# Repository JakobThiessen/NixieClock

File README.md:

# NixieClock

# Hardware

Wichtig: Ohne Änderung tut die SD karte nicht. (Betrifft nur V2.0 in der V2.1 sind die Änderung im Layout schon umgesetzt)

## Display 1.14"

| Top side                |Bottom side               |
|-----------------------:|:-------------------------:|
|  |  |

## Display 1.8"

| Top side                |Bottom side               |
|-----------------------:|:-------------------------:|
|  |  |

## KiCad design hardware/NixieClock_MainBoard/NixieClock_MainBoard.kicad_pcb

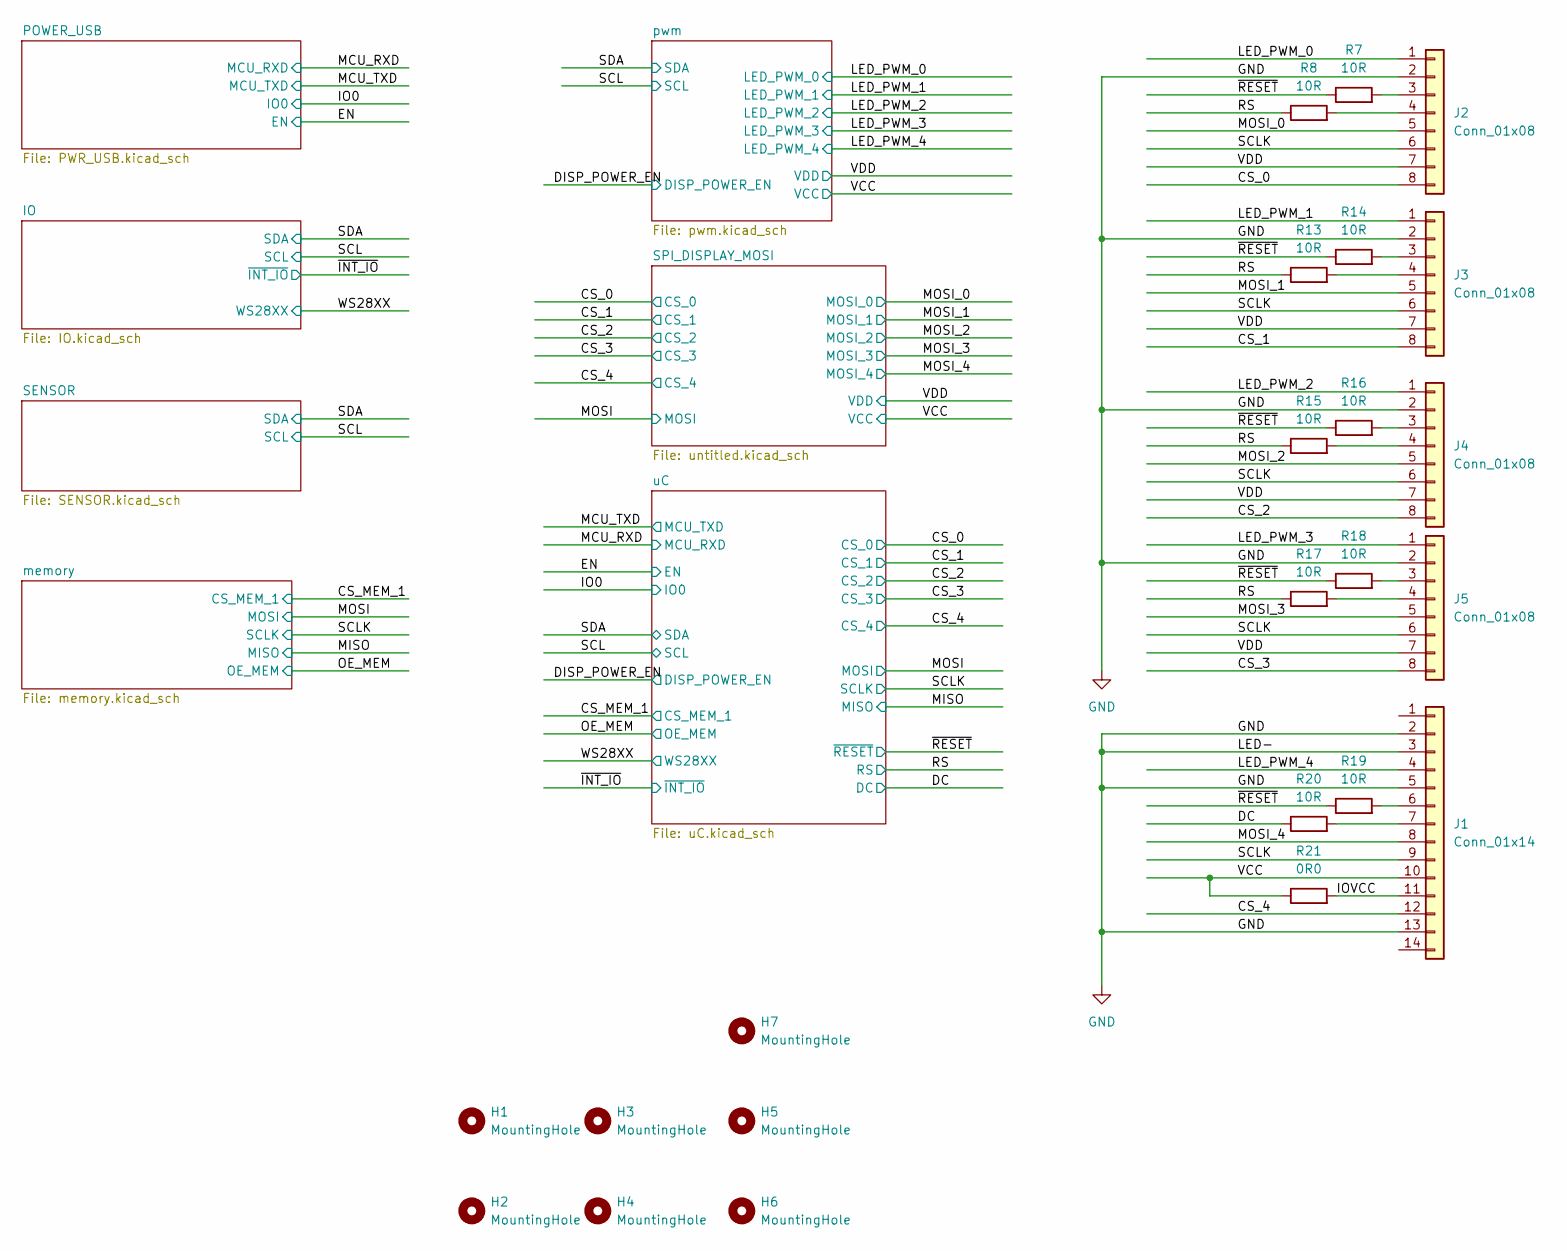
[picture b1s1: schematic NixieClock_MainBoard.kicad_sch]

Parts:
H1, H2, H3, H4, H5, H6, H7: MountingHole; MountingHole_3.2mm_M3
J1: Conn_01x14; PinSocket_1x14_P1.27mm_Vertical
J2, J3, J4, J5: Conn_01x08; PinSocket_1x08_P1.27mm_Vertical
R7, R8, R13, R14, R15, R16, R17, R18, R19, R20: 10R; R_0603_1608Metric
R21: 0R0; R_0603_1608Metric

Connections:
/CS_0: J2.8; also elsewhere on the board
/CS_1: J3.8; also elsewhere on the board
/CS_2: J4.8; also elsewhere on the board
/CS_3: J5.8; also elsewhere on the board
/CS_4: J1.12; also elsewhere on the board
/DC: R20.1; also elsewhere on the board
/IOVCC: J1.11, R21.2
/LED_PWM_0: J2.1; also elsewhere on the board
/LED_PWM_1: J3.1; also elsewhere on the board
/LED_PWM_2: J4.1; also elsewhere on the board
/LED_PWM_3: J5.1; also elsewhere on the board
/LED_PWM_4: J1.4; also elsewhere on the board
/MOSI_0: J2.5; also elsewhere on the board
/MOSI_1: J3.5; also elsewhere on the board
/MOSI_2: J4.5; also elsewhere on the board
/MOSI_3: J5.5; also elsewhere on the board
/MOSI_4: J1.8; also elsewhere on the board
/RS: R8.1, R13.1, R15.1, R17.1; also elsewhere on the board
/SCLK: J1.9, J2.6, J3.6, J4.6, J5.6; also elsewhere on the board
/VCC: J1.10, R21.1; also elsewhere on the board
/VDD: J2.7, J3.7, J4.7, J5.7; also elsewhere on the board
/~RESET: R7.1, R14.1, R16.1, R18.1, R19.1; also elsewhere on the board
GND: J1.2, J1.3, J1.5, J1.13, J2.2, J3.2, J4.2, J5.2; also elsewhere on the board
unnamed: J1.6, R19.2
unnamed: J1.7, R20.2
unnamed: J2.3, R7.2
unnamed: J2.4, R8.2
unnamed: J3.3, R14.2
unnamed: J3.4, R13.2
unnamed: J4.3, R16.2
unnamed: J4.4, R15.2
unnamed: J5.3, R18.2
unnamed: J5.4, R17.2

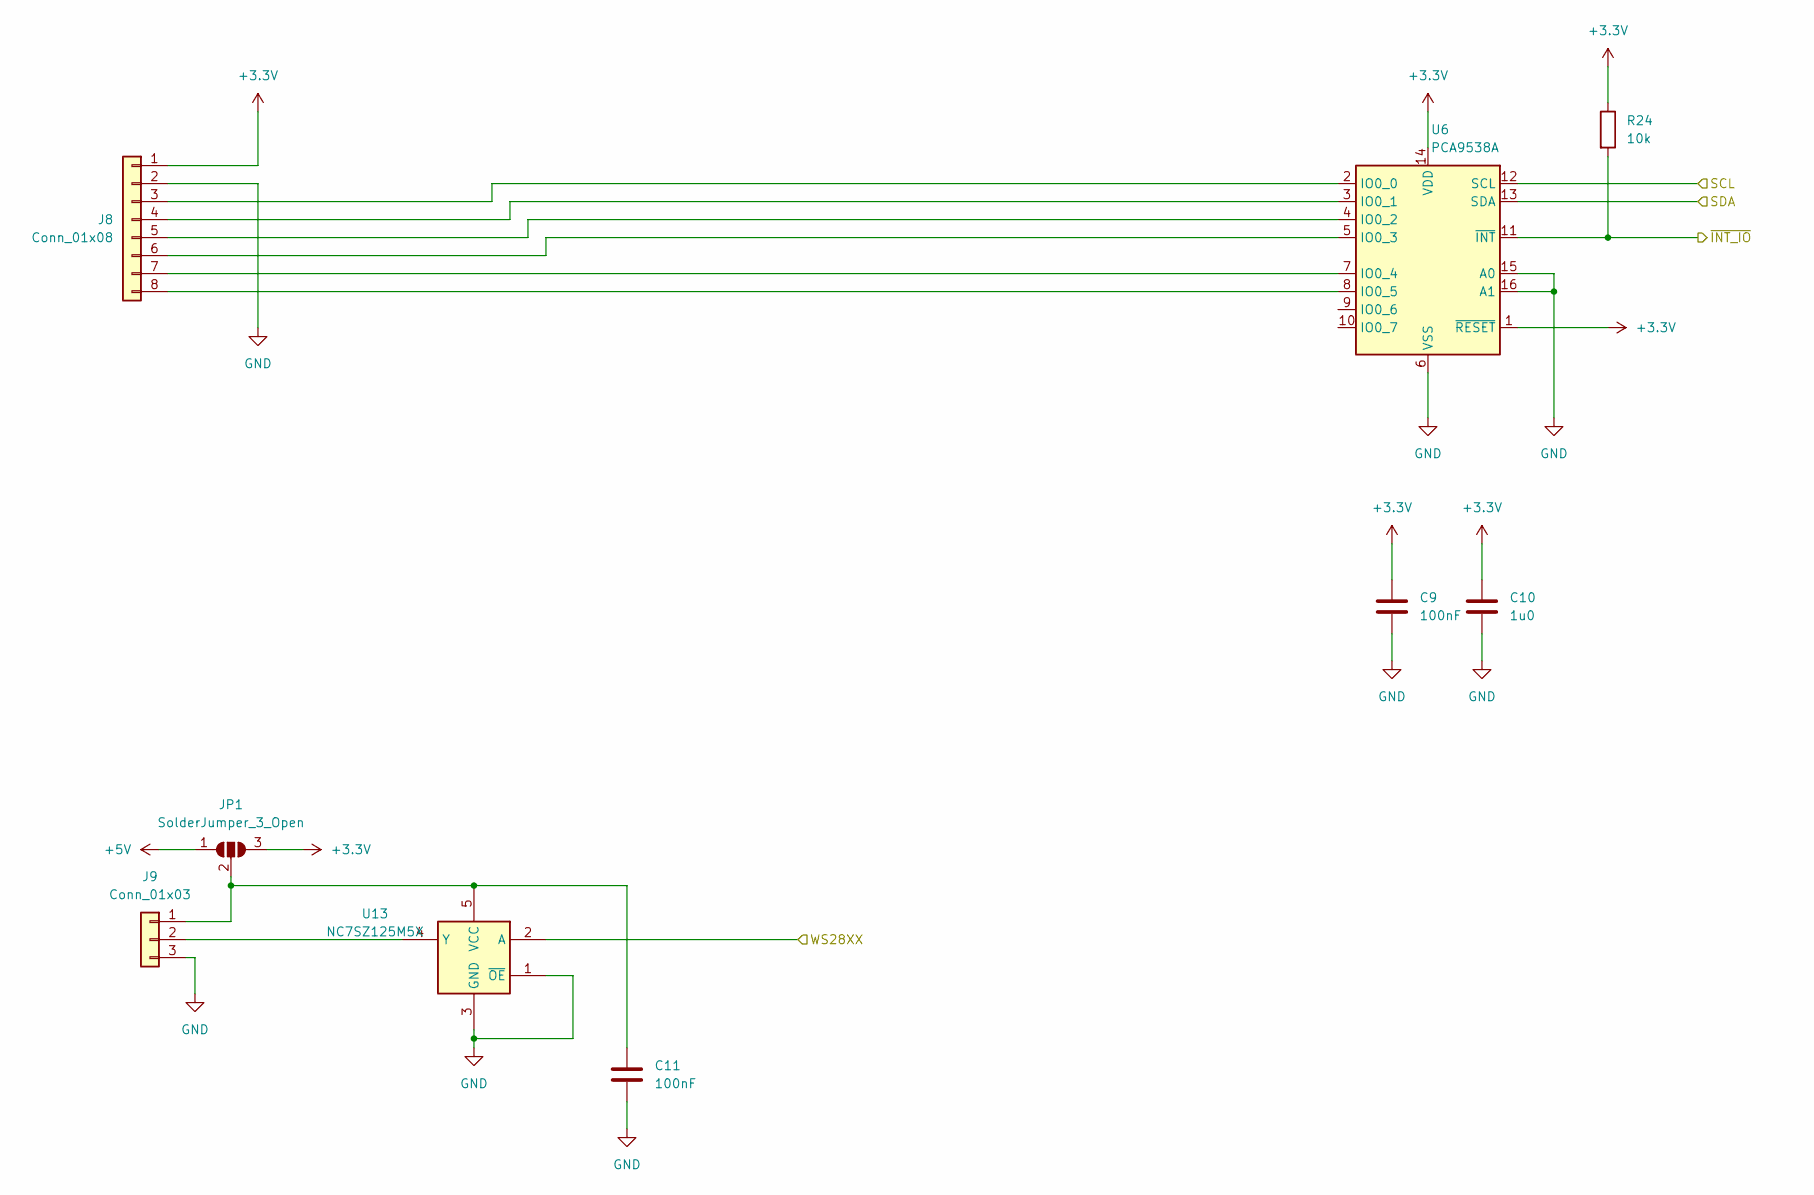
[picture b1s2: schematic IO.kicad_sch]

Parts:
C9, C11: 100nF; C_0603_1608Metric
C10: 1u0; C_0603_1608Metric
J8: Conn_01x08; PinHeader_1x08_P2.54mm_Vertical
J9: Conn_01x03; PinHeader_1x03_P2.54mm_Vertical
JP1: SolderJumper_3_Open; SolderJumper-3_P1.3mm_Open_Pad1.0x1.5mm
R24: 10k; R_0603_1608Metric
U6: PCA9538A; HVQFN-16-1EP_3x3mm_P0.5mm_EP1.5x1.5mm
U13: NC7SZ125M5X; SOT-23-5

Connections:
+3.3V: C9.1, C10.1, J8.1, JP1.3 (B), R24.1, U6.1 (~RESET), U6.14 (VDD); also elsewhere on the board
+5V: JP1.1 (A); also elsewhere on the board
/SCL: U6.12 (SCL); also elsewhere on the board
/SDA: U6.13 (SDA); also elsewhere on the board
/WS28XX: U13.2 (A); also elsewhere on the board
/~INT_IO: R24.2, U6.11 (~INT); also elsewhere on the board
GND: C9.2, C10.2, C11.2, J8.2, J9.3, U6.6 (VSS), U6.15 (A0), U6.16 (A1), U13.1 (~OE), U13.3 (GND); also elsewhere on the board
unnamed: J8.3, U6.2 (IO0_0)
unnamed: J8.4, U6.3 (IO0_1)
unnamed: J8.5, U6.4 (IO0_2)
unnamed: J8.6, U6.5 (IO0_3)
unnamed: J8.7, U6.7 (IO0_4)
unnamed: J8.8, U6.8 (IO0_5)
unnamed: C11.1, J9.1, JP1.2 (C), U13.5 (VCC)
unnamed: J9.2, U13.4 (Y)

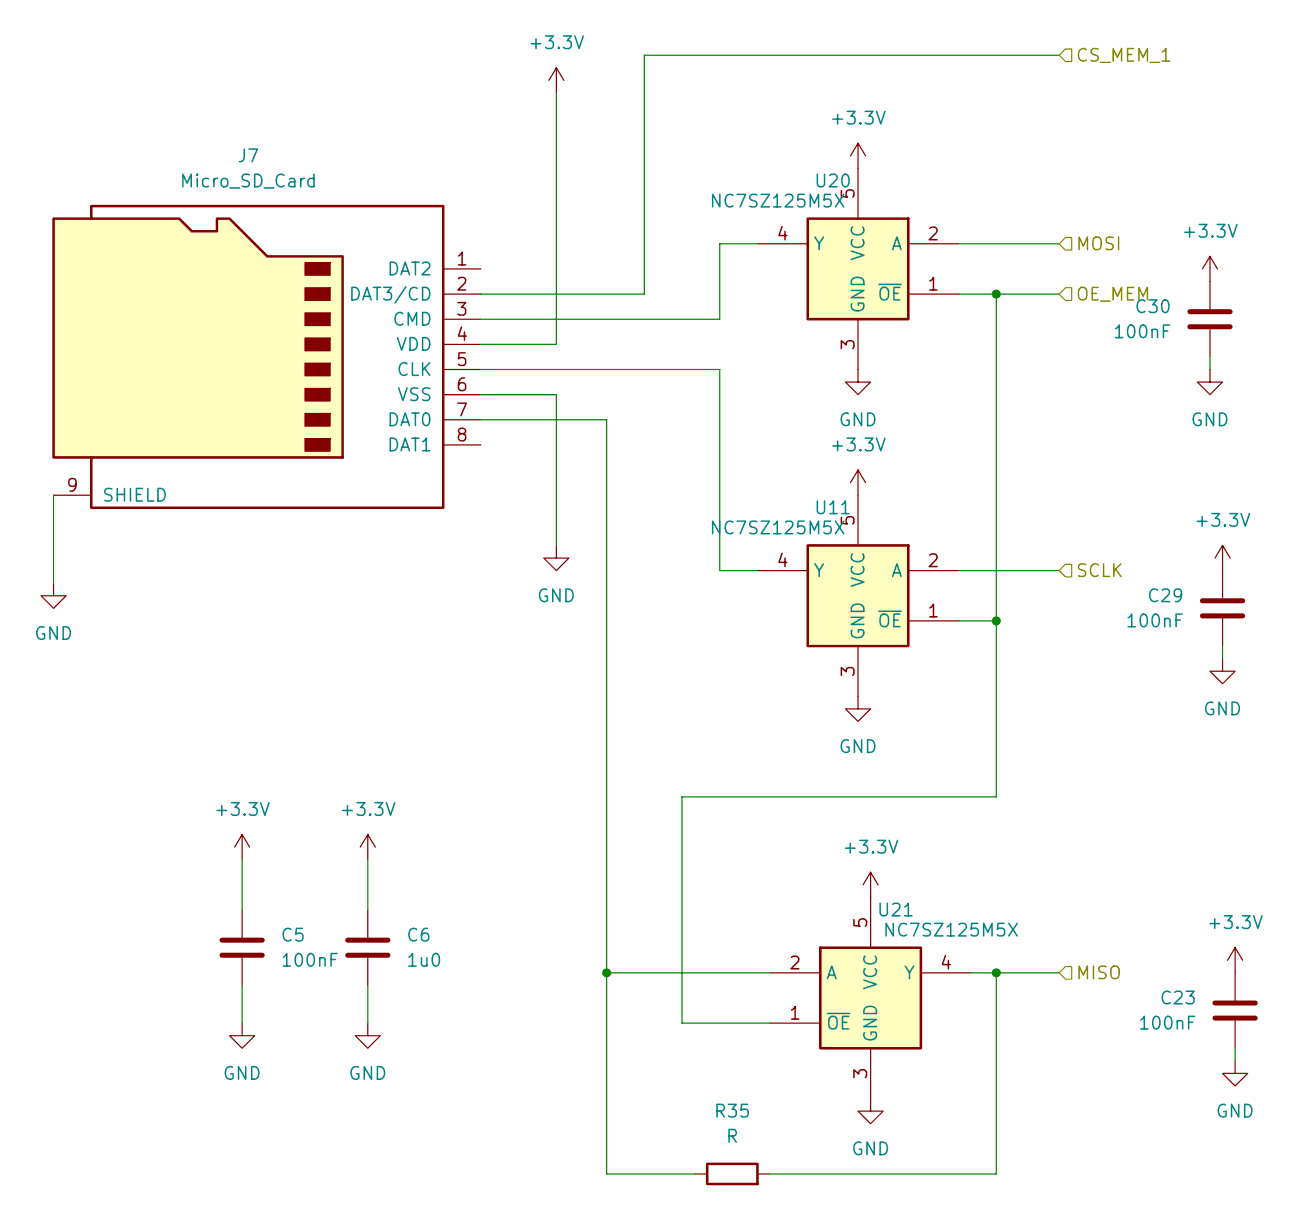
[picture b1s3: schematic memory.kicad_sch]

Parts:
C5, C23, C29, C30: 100nF; C_0603_1608Metric
C6: 1u0; C_0603_1608Metric
J7: Micro_SD_Card; microSD_HC_Hirose_DM3D-SF
R35: R; R_0603_1608Metric
U11, U20, U21: NC7SZ125M5X; SOT-23-5

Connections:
+3.3V: C5.1, C6.1, C23.1, C29.1, C30.1, J7.4 (VDD), U11.5 (VCC), U20.5 (VCC), U21.5 (VCC); also elsewhere on the board
/CS_MEM_1: J7.2 (DAT3/CD); also elsewhere on the board
/MISO: R35.2, U21.4 (Y); also elsewhere on the board
/MOSI: U20.2 (A); also elsewhere on the board
/OE_MEM: U11.1 (~OE), U20.1 (~OE), U21.1 (~OE); also elsewhere on the board
/SCLK: U11.2 (A); also elsewhere on the board
GND: C5.2, C6.2, C23.2, C29.2, C30.2, J7.6 (VSS), J7.9 (SHIELD), U11.3 (GND), U20.3 (GND), U21.3 (GND); also elsewhere on the board
unnamed: J7.5 (CLK), U11.4 (Y)
unnamed: J7.3 (CMD), U20.4 (Y)
unnamed: J7.7 (DAT0), R35.1, U21.2 (A)

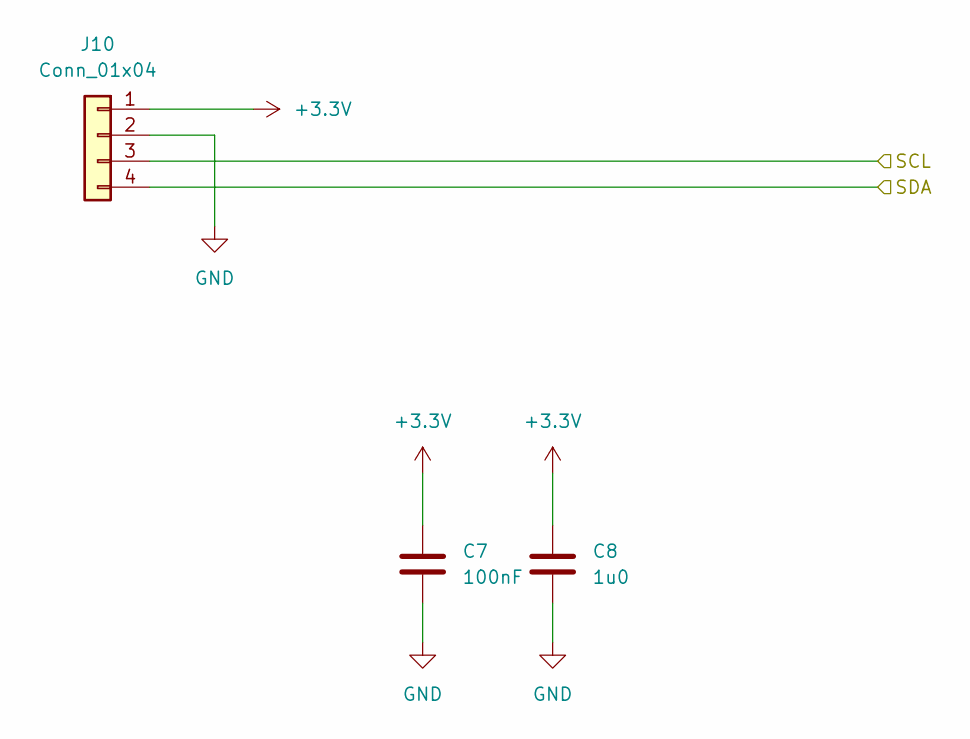
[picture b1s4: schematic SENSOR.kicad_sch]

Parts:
C7: 100nF; C_0603_1608Metric
C8: 1u0; C_0603_1608Metric
J10: Conn_01x04; PinHeader_1x04_P2.54mm_Vertical

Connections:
+3.3V: C7.1, C8.1, J10.1; also elsewhere on the board
/SCL: J10.3; also elsewhere on the board
/SDA: J10.4; also elsewhere on the board
GND: C7.2, C8.2, J10.2; also elsewhere on the board

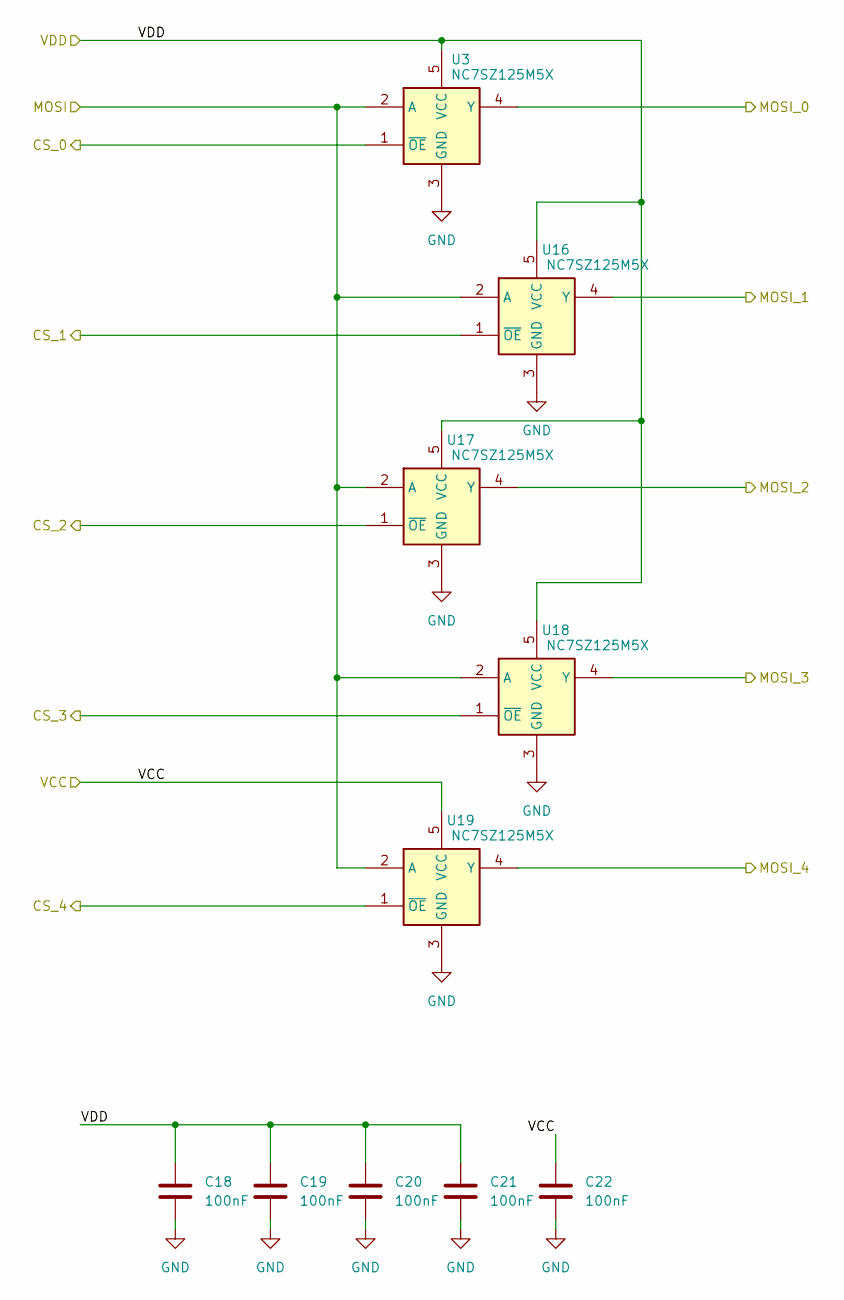
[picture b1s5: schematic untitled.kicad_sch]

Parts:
C18, C19, C20, C21, C22: 100nF; C_0603_1608Metric
U3, U16, U17, U18, U19: NC7SZ125M5X; SOT-23-5

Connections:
/CS_0: U3.1 (~OE); also elsewhere on the board
/CS_1: U16.1 (~OE); also elsewhere on the board
/CS_2: U17.1 (~OE); also elsewhere on the board
/CS_3: U18.1 (~OE); also elsewhere on the board
/CS_4: U19.1 (~OE); also elsewhere on the board
/MOSI: U3.2 (A), U16.2 (A), U17.2 (A), U18.2 (A), U19.2 (A); also elsewhere on the board
/MOSI_0: U3.4 (Y); also elsewhere on the board
/MOSI_1: U16.4 (Y); also elsewhere on the board
/MOSI_2: U17.4 (Y); also elsewhere on the board
/MOSI_3: U18.4 (Y); also elsewhere on the board
/MOSI_4: U19.4 (Y); also elsewhere on the board
/VCC: C22.1, U19.5 (VCC); also elsewhere on the board
/VDD: C18.1, C19.1, C20.1, C21.1, U3.5 (VCC), U16.5 (VCC), U17.5 (VCC), U18.5 (VCC); also elsewhere on the board
GND: C18.2, C19.2, C20.2, C21.2, C22.2, U3.3 (GND), U16.3 (GND), U17.3 (GND), U18.3 (GND), U19.3 (GND); also elsewhere on the board

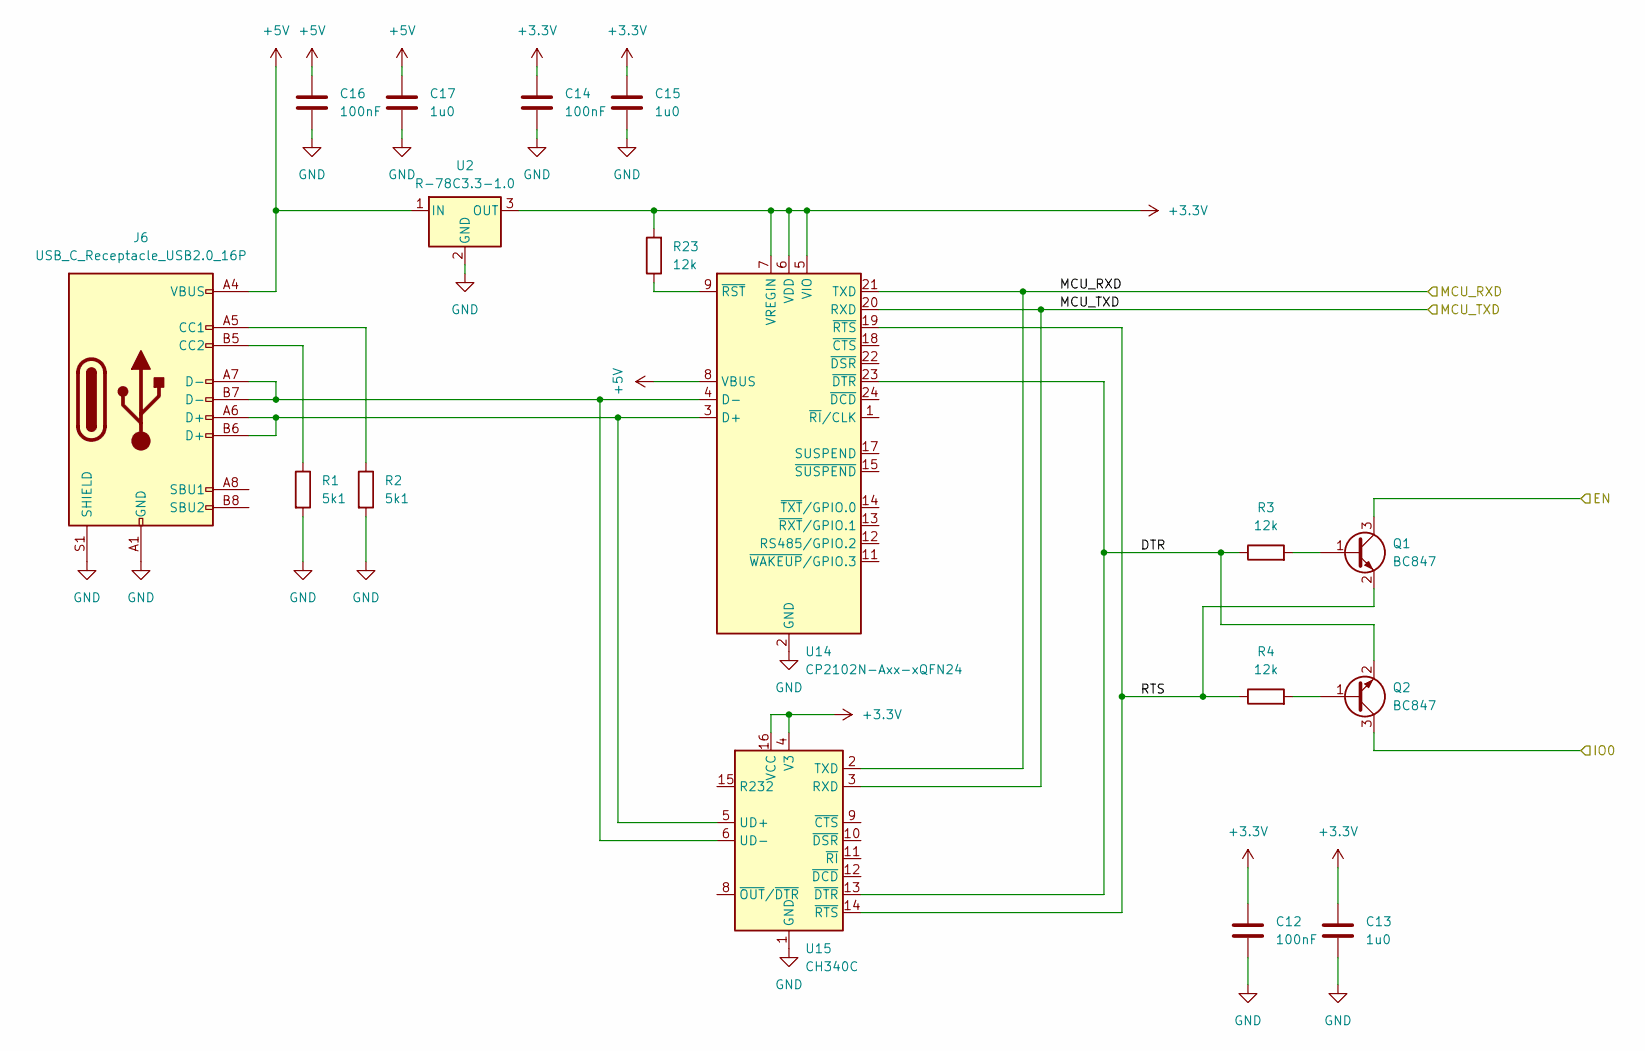
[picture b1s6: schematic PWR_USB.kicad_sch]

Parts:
C12, C14, C16: 100nF; C_0603_1608Metric
C13, C15, C17: 1u0; C_0603_1608Metric
J6: USB_C_Receptacle_USB2.0_16P; USB_C_Receptacle_GCT_USB4110
Q1, Q2: BC847; SOT-23
R1, R2: 5k1; R_0603_1608Metric
R3, R4, R23: 12k; R_0603_1608Metric
U2: R-78C3.3-1.0; Converter_DCDC_RECOM_R-78E-0.5_THT
U14: CP2102N-Axx-xQFN24; QFN-24-1EP_4x4mm_P0.5mm_EP2.6x2.6mm
U15: CH340C; SOIC-16_3.9x9.9mm_P1.27mm

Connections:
+3.3V: C12.1, C13.1, C14.1, C15.1, R23.2, U2.3 (OUT), U14.5 (VIO), U14.6 (VDD), U14.7 (VREGIN), U15.4 (V3), U15.16 (VCC); also elsewhere on the board
+5V: C16.1, C17.1, J6.A4 (VBUS), J6.A9 (VBUS), J6.B4 (VBUS), J6.B9 (VBUS), U2.1 (IN), U14.8 (VBUS); also elsewhere on the board
/EN: Q1.3 (C); also elsewhere on the board
/IO0: Q2.3 (C); also elsewhere on the board
/MCU_RXD: U14.21 (TXD), U15.2 (TXD); also elsewhere on the board
/MCU_TXD: U14.20 (RXD), U15.3 (RXD); also elsewhere on the board
/POWER_USB/DTR: Q2.2 (E), R3.1, U14.23 (~DTR), U15.13 (~DTR)
/POWER_USB/RTS: Q1.2 (E), R4.1, U14.19 (~RTS), U15.14 (~RTS)
GND: C12.2, C13.2, C14.2, C15.2, C16.2, C17.2, J6.A1 (GND), J6.A12 (GND), J6.B1 (GND), J6.B12 (GND), J6.S1 (SHIELD), R1.2, R2.2, U2.2 (GND), U14.2 (GND), U14.25 (GND), U15.1 (GND); also elsewhere on the board
unnamed: J6.A5 (CC1), R2.1
unnamed: J6.B5 (CC2), R1.1
unnamed: Q1.1 (B), R3.2
unnamed: Q2.1 (B), R4.2
unnamed: J6.A6 (D+), J6.B6 (D+), U14.3 (D+), U15.5 (UD+)
unnamed: J6.A7 (D-), J6.B7 (D-), U14.4 (D-), U15.6 (UD-)
unnamed: R23.1, U14.9 (~RST)

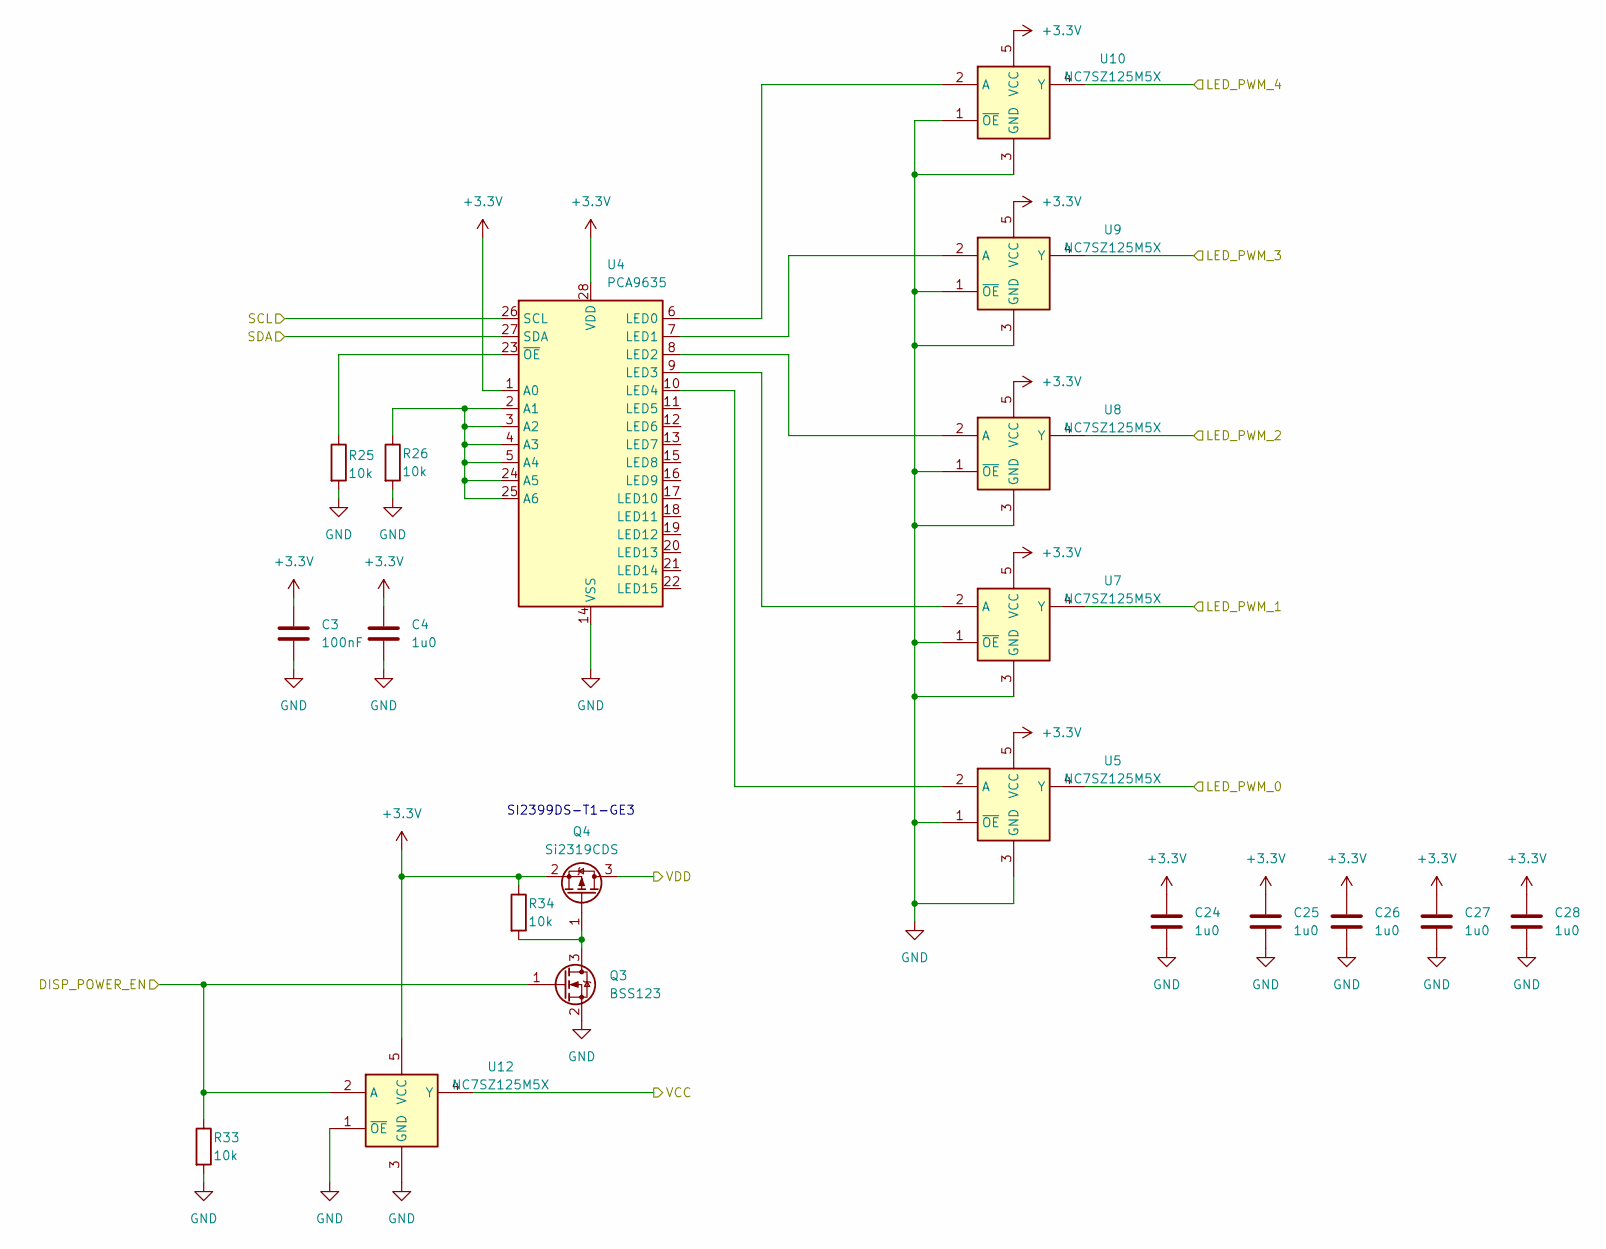
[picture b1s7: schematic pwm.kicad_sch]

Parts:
C3: 100nF; C_0603_1608Metric
C4, C24, C25, C26, C27, C28: 1u0; C_0603_1608Metric
Q3: BSS123; SOT-23
Q4: Si2319CDS; SOT-23
R25, R26, R33, R34: 10k; R_0603_1608Metric
U4: PCA9635; TSSOP-28_4.4x9.7mm_P0.65mm
U5, U7, U8, U9, U10, U12: NC7SZ125M5X; SOT-23-5

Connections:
+3.3V: C3.1, C4.1, C24.1, C25.1, C26.1, C27.1, C28.1, Q4.2 (S), R34.1, U4.1 (A0), U4.28 (VDD), U5.5 (VCC), U7.5 (VCC), U8.5 (VCC), U9.5 (VCC), U10.5 (VCC), U12.5 (VCC); also elsewhere on the board
/DISP_POWER_EN: Q3.1 (G), R33.1, U12.2 (A); also elsewhere on the board
/LED_PWM_0: U5.4 (Y); also elsewhere on the board
/LED_PWM_1: U7.4 (Y); also elsewhere on the board
/LED_PWM_2: U8.4 (Y); also elsewhere on the board
/LED_PWM_3: U9.4 (Y); also elsewhere on the board
/LED_PWM_4: U10.4 (Y); also elsewhere on the board
/SCL: U4.26 (SCL); also elsewhere on the board
/SDA: U4.27 (SDA); also elsewhere on the board
/VCC: U12.4 (Y); also elsewhere on the board
/VDD: Q4.3 (D); also elsewhere on the board
GND: C3.2, C4.2, C24.2, C25.2, C26.2, C27.2, C28.2, Q3.2 (S), R25.2, R26.2, R33.2, U4.14 (VSS), U5.1 (~OE), U5.3 (GND), U7.1 (~OE), U7.3 (GND), U8.1 (~OE), U8.3 (GND), U9.1 (~OE), U9.3 (GND), U10.1 (~OE), U10.3 (GND), U12.1 (~OE), U12.3 (GND); also elsewhere on the board
unnamed: Q3.3 (D), Q4.1 (G), R34.2
unnamed: R26.1, U4.2 (A1), U4.3 (A2), U4.4 (A3), U4.5 (A4), U4.24 (A5), U4.25 (A6)
unnamed: U4.7 (LED1), U9.2 (A)
unnamed: U4.8 (LED2), U8.2 (A)
unnamed: U4.9 (LED3), U7.2 (A)
unnamed: U4.10 (LED4), U5.2 (A)
unnamed: R25.1, U4.23 (~OE)
unnamed: U4.6 (LED0), U10.2 (A)

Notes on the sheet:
SI2399DS-T1-GE3

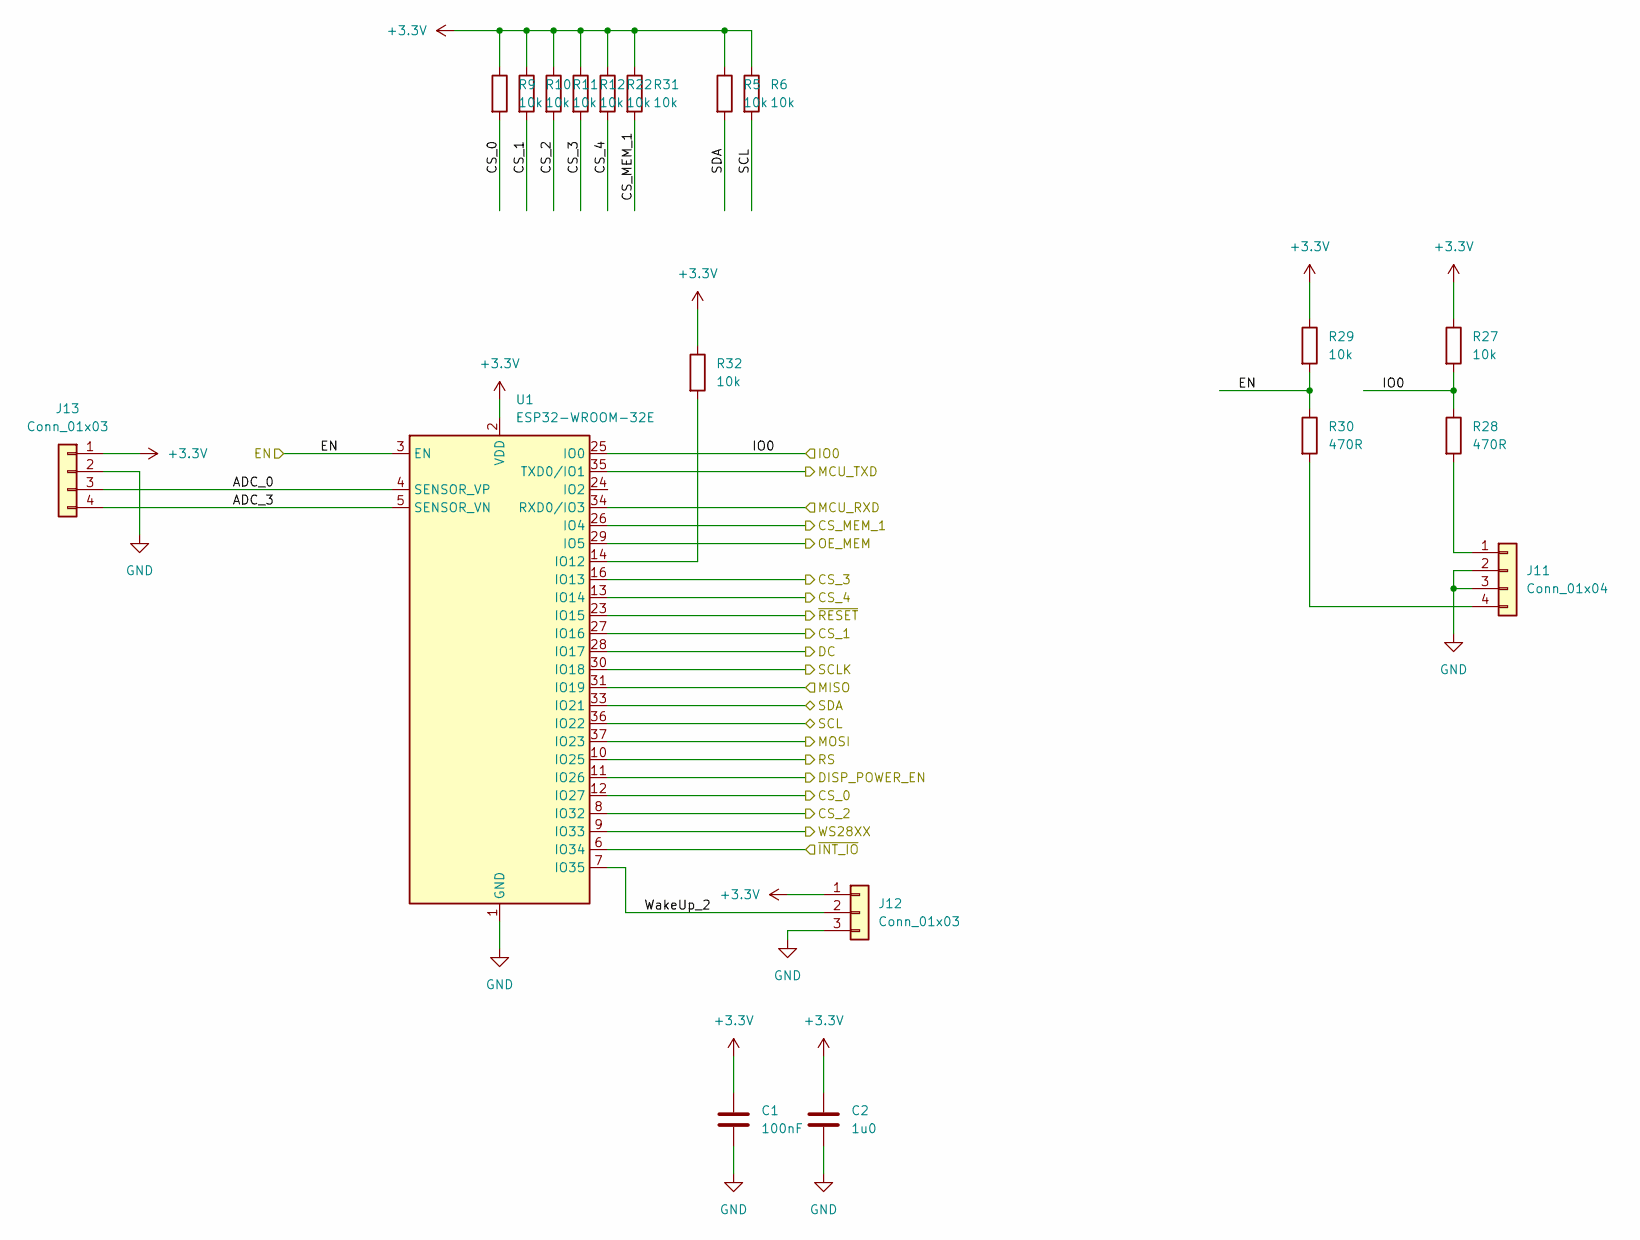
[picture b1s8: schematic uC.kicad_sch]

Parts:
C1: 100nF; C_0603_1608Metric
C2: 1u0; C_0603_1608Metric
J11: Conn_01x04; PinHeader_1x04_P2.54mm_Vertical_SMD_Pin1Left
J12: Conn_01x03; PinHeader_1x03_P2.54mm_Vertical
J13: Conn_01x03; PinHeader_1x04_P2.54mm_Vertical
R5, R6, R9, R10, R11, R12, R22, R27, R29, R31, R32: 10k; R_0603_1608Metric
R28, R30: 470R; R_0603_1608Metric
U1: ESP32-WROOM-32E; ESP32-WROOM-32D

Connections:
+3.3V: C1.1, C2.1, J12.1, J13.1, R5.1, R6.1, R9.1, R10.1, R11.1, R12.1, R22.1, R27.1, R29.1, R31.1, R32.1, U1.2 (VDD); also elsewhere on the board
/CS_0: R9.2, U1.12 (IO27); also elsewhere on the board
/CS_1: R10.2, U1.27 (IO16); also elsewhere on the board
/CS_2: R11.2, U1.8 (IO32); also elsewhere on the board
/CS_3: R12.2, U1.16 (IO13); also elsewhere on the board
/CS_4: R22.2, U1.13 (IO14); also elsewhere on the board
/CS_MEM_1: R31.2, U1.26 (IO4); also elsewhere on the board
/DC: U1.28 (IO17); also elsewhere on the board
/DISP_POWER_EN: U1.11 (IO26); also elsewhere on the board
/EN: R29.2, R30.1, U1.3 (EN); also elsewhere on the board
/IO0: R27.2, R28.1, U1.25 (IO0); also elsewhere on the board
/MCU_RXD: U1.34 (RXD0/IO3); also elsewhere on the board
/MCU_TXD: U1.35 (TXD0/IO1); also elsewhere on the board
/MISO: U1.31 (IO19); also elsewhere on the board
/MOSI: U1.37 (IO23); also elsewhere on the board
/OE_MEM: U1.29 (IO5); also elsewhere on the board
/RS: U1.10 (IO25); also elsewhere on the board
/SCL: R6.2, U1.36 (IO22); also elsewhere on the board
/SCLK: U1.30 (IO18); also elsewhere on the board
/SDA: R5.2, U1.33 (IO21); also elsewhere on the board
/WS28XX: U1.9 (IO33); also elsewhere on the board
/uC/ADC_0: J13.3, U1.4 (SENSOR_VP)
/uC/ADC_3: J13.4, U1.5 (SENSOR_VN)
/uC/WakeUp_2: J12.2, U1.7 (IO35)
/~INT_IO: U1.6 (IO34); also elsewhere on the board
/~RESET: U1.23 (IO15); also elsewhere on the board
GND: C1.2, C2.2, J11.2, J11.3, J12.3, J13.2, U1.1 (GND), U1.15 (GND), U1.38 (GND), U1.39 (GND); also elsewhere on the board
unnamed: J11.1, R28.2
unnamed: J11.4, R30.2
unnamed: R32.2, U1.14 (IO12)

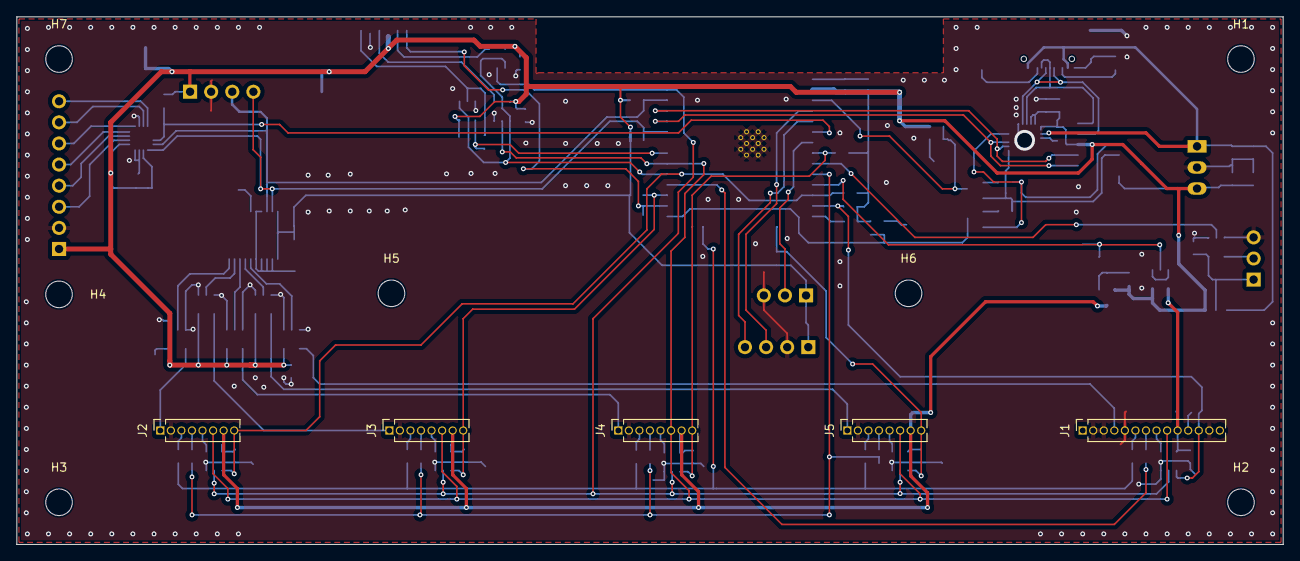
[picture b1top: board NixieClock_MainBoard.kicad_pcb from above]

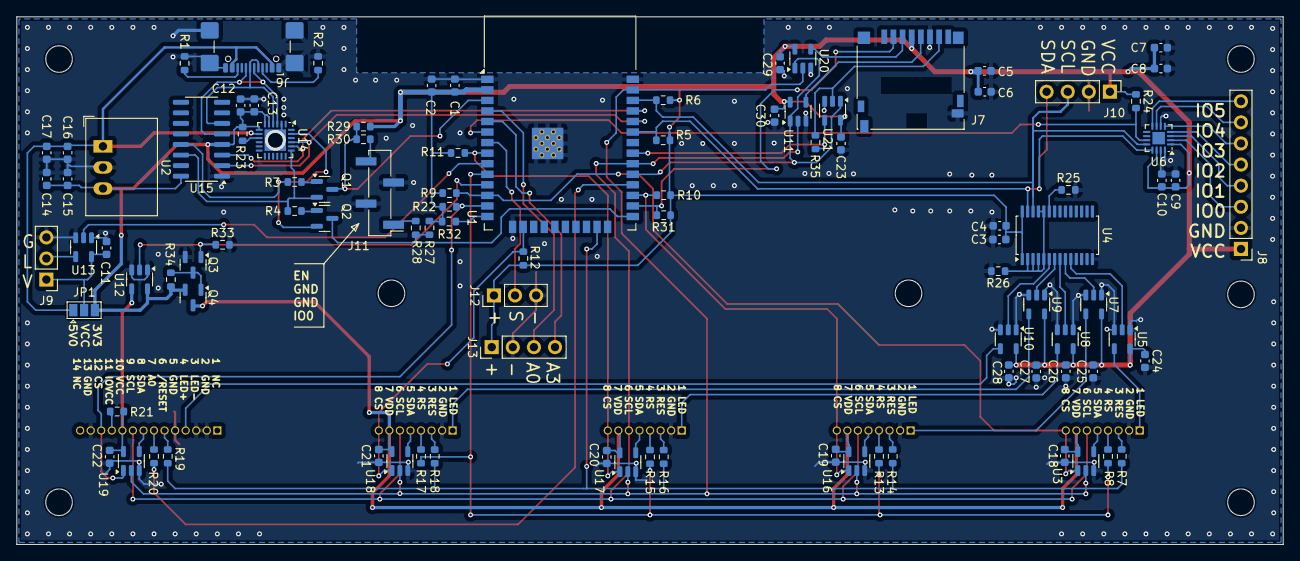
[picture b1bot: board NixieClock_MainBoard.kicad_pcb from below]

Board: 2 copper layers, 152.4 x 63.5 mm, 111 parts (99 on the bottom side), 82 nets.

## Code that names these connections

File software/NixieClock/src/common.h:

#ifndef COMMON_CONFIG_h
#define COMMON_CONFIG_h

#include <stdint.h>
#include "freertos/FreeRTOS.h"
#include "freertos/FreeRTOSConfig.h"
#include "freertos/task.h"
#include "freertos/queue.h"

#include <time.h>

#ifdef __cplusplus
extern "C" {
#endif

/**************************** */
/*** DEFINES              *** */
/**************************** */

#define CONFIG_FREERTOS_USE_STATS_FORMATTING_FUNCTIONS 1
#define CONFIG_FREERTOS_USE_TRACE_FACILITY 1

#define TFT_MOSI        23
#define TFT_MISO        19
#define TFT_CLK         18
#define TFT_RST         -1 // set to -1 and connect to Arduino RESET pin
#define TFT_DC          25
#define TFT_DC_2        17
#define TFT_RESET       15

#define TFT_CS_0        27
#define TFT_CS_1        16
#define TFT_CS_2        32
#define TFT_CS_3        13
#define TFT_CS_4        14

#define SD_CS           5
#define SD_BUF_OE       4   // /OE der 74LVC1G125 Tristate-Buffer (LOW=aktiv)
#define DISPLAY_POW_EN  26

#define LED_PIN         33

#define INT_IO_PIN      34
#define WAKE_UP_PIN     35

#define ADC_0_PIN       36  // ADC1
#define ADC_3_PIN       39  // ADC1

#define SPI_FREQUENCY 16000000U

// ─── I2C bus (PCA9538A button expander + PCA9685 backlight) ──────────────────
#define I2C_SDA_PIN     21
#define I2C_SCL_PIN     22

#define FW_VERSION "5.12.0"
#define FW_BUILD_DATE __DATE__
#define FW_BUILD_TIME __TIME__

#define SD_CACHE_MAX 128

// SD background image limits (24-bit BMP only)
#define BG_IMAGE_MAX_FILE_SIZE  (100UL * 1024UL)  // max file size on SD
#define BG_IMAGE_MAX_W          160               // max image width  (px)
#define BG_IMAGE_MAX_H          128               // max image height (px)



typedef struct {
    char path[128];
    char name[64];
    bool isDir;
    uint32_t size;
} SdCacheEntry;

extern SemaphoreHandle_t xSpiMutex;
extern SemaphoreHandle_t xI2cMutex;   // protects Wire (I2C) bus shared between PCA9685 + PCA9538A
extern QueueHandle_t xQueue_RGB_Config;
extern QueueHandle_t xQueue_WiFi;

typedef struct{
    uint8_t rgbBrigthness;
    bool rgbSwitch;
    uint16_t rgbMode;
    uint8_t rgbR;
    uint8_t rgbG;
    uint8_t rgbB;
}rgbConfigStruct;

typedef struct{
    bool wifiConnected;
    IPAddress ip;
    bool sdCardDetected;
    uint16_t displayBrightness;
    uint16_t displayIntervalSec;
    char ntpServer[64];
    int8_t utcOffset;
    bool slideshowEnabled;
    bool calendarEnabled;
    bool backgroundEnabled;
    uint8_t bootAnimMode;
    uint8_t clockFgR;
    uint8_t clockFgG;
    uint8_t clockFgB;
    uint8_t clockBgR;
    uint8_t clockBgG;
    uint8_t clockBgB;
    bool weatherEnabled;
    char weatherCity[32];
    float weatherLat;
    float weatherLon;
    char bgImagePath[128];  // SD path to background BMP; empty = none
    bool bgTextDark;        // true = dark text (use for light-coloured images)
}systemConfigStruct;

typedef struct{
    float temperature;
    uint8_t weatherCode;
    unsigned long lastFetchMs;
    bool valid;
}weatherDataStruct;


typedef struct{
    uint8_t dayList[30];
    uint8_t monthList[30];
}calendarPublicHolidays;

typedef struct{
    uint16_t displayBrightness;

    int8_t clockUTC;
    bool clockAnimation;
    char* clockAnimatinoPicturePath;
    bool clockDigitNumber;
    bool clockDigitPicture;
    char* clockDigitPicturePath;
    bool clockDigitNumberUnicolored;
    uint16_t clockDigitNumberColor;
    bool clockDigitMulticolored;
    uint16_t* clockDigitMulticoredList;
    char* clockBackground;

    //Variables for Calendar
    bool calendarUseBackgroundPicture;
    char* calendarBackgroudPath;
    uint16_t calendarBackGroundColor;
    bool calendarAnimation;
    char* calendarAnimatinoPicturePath;

    bool caldarUseGooleCalender;
    char* calendarGoogleAPI_KEY;

    struct calendarPublicHolidays;
}clockConfiguration;

extern volatile bool bootInitDone;
extern rgbConfigStruct rgbConfig;
extern systemConfigStruct systemConfig;
extern clockConfiguration clockConfig;
extern weatherDataStruct weatherData;
extern uint16_t* bgImageData;  // RGB565 buffer of loaded background; nullptr if none
extern uint16_t  bgImageW;     // width of loaded image in pixels
extern uint16_t  bgImageH;     // height of loaded image in pixels

#ifdef __cplusplus
}
#endif

// C++ only: saves all current settings as JSON to /settings.json on the SD card.
// Thread-safe: takes xSpiMutex internally. Returns true on success. No-op if SD absent.
#ifdef __cplusplus
bool saveConfigToSD();
// Load BMP from systemConfig.bgImagePath into bgImageData (RGB565 heap buffer).
// Thread-safe: acquires xSpiMutex internally. Call after bootInitDone is set.
bool loadBgImage();
#endif

#endif /* COMMON_CONFIG_h */
